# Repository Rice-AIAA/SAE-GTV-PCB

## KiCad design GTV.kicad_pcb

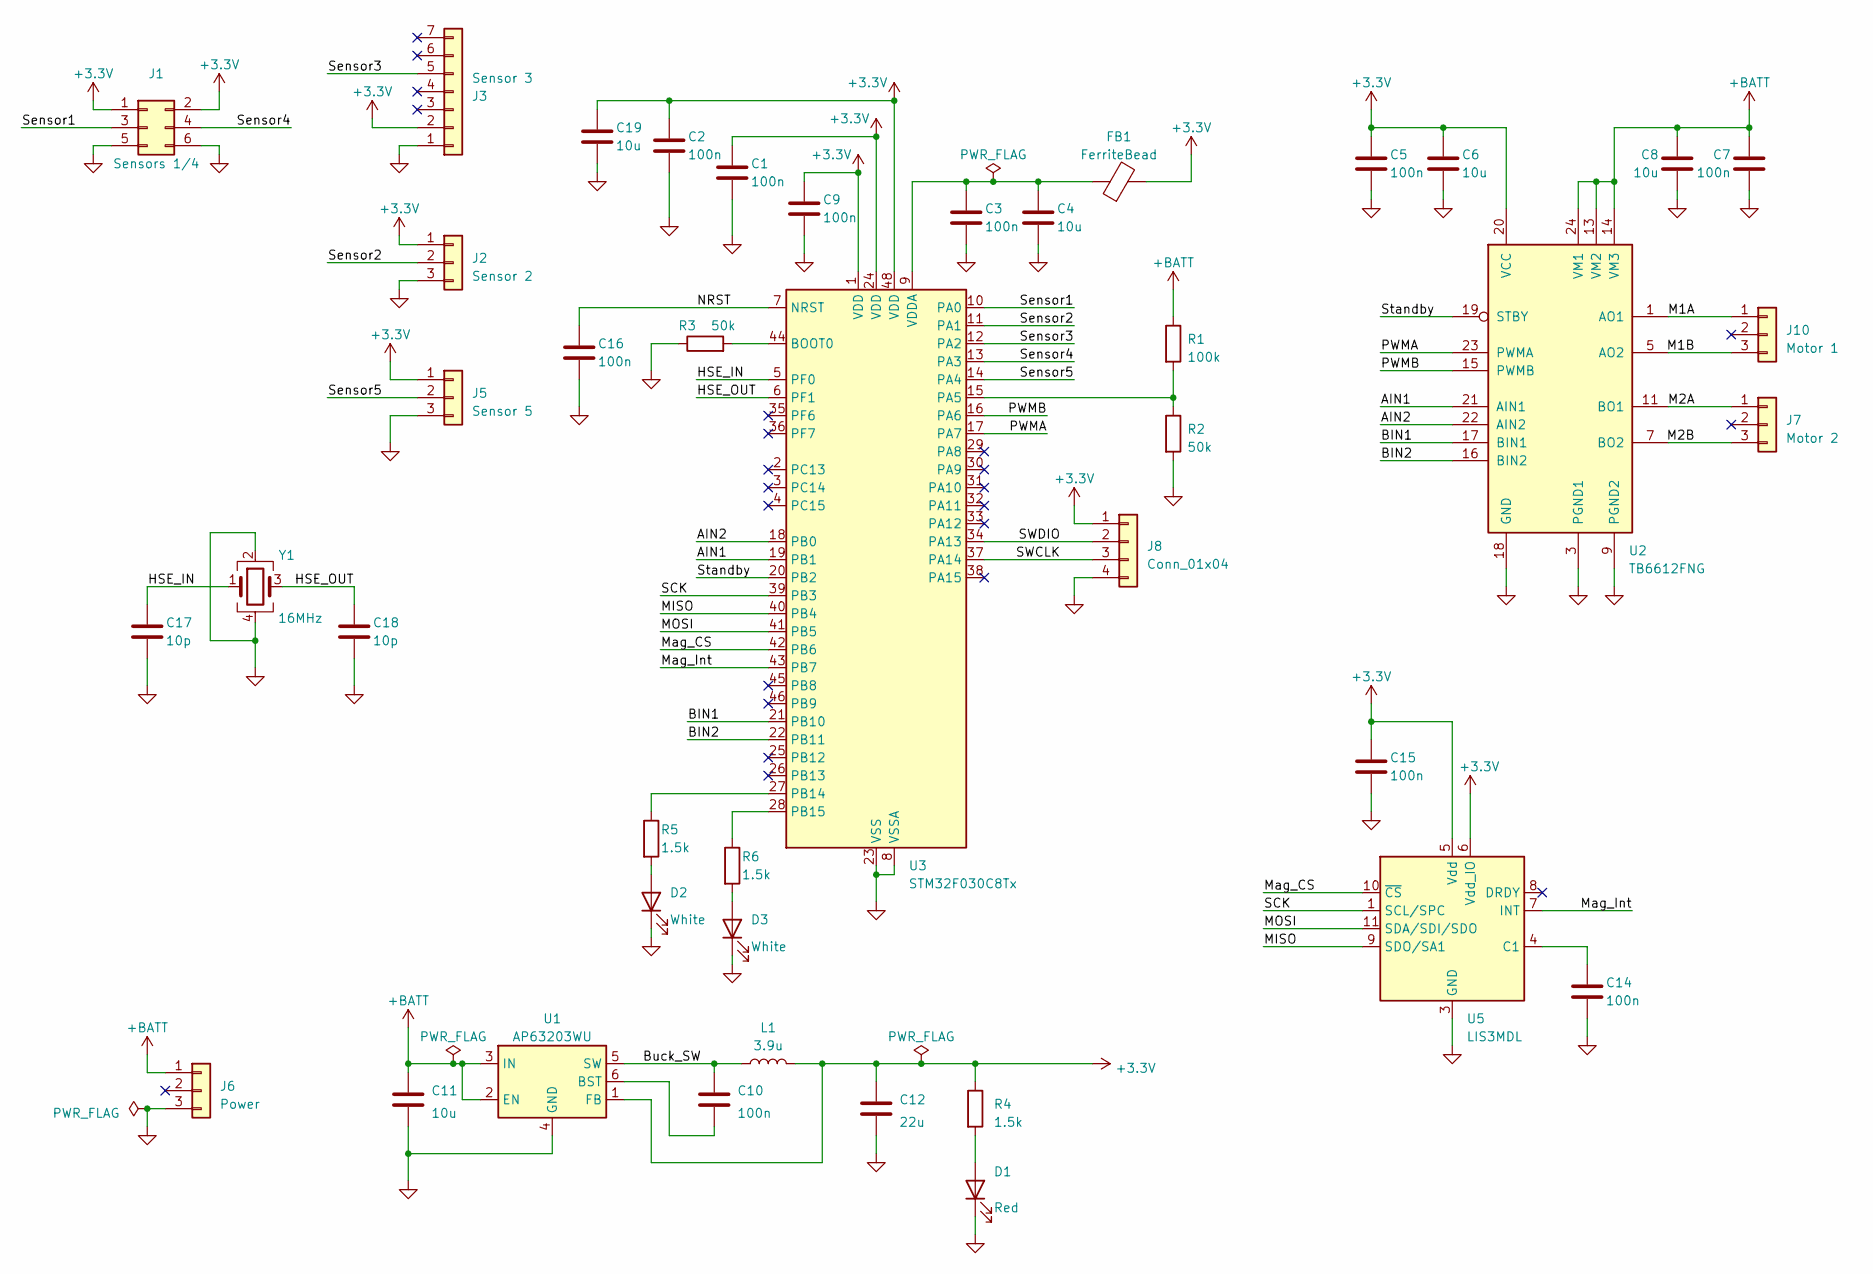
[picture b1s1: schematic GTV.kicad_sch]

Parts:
C1, C2, C3, C5, C7, C9, C10, C14, C15, C16: 100n; C_0402_1005Metric
C4, C6, C8, C19: 10u; C_0603_1608Metric
C11: 10u; C_0805_2012Metric
C12: 22u; C_0805_2012Metric
C17, C18: 10p; C_0402_1005Metric
D1: Red; LED_0603_1608Metric
D2, D3: White; LED_0603_1608Metric
FB1: FerriteBead; L_0805_2012Metric
J1: Sensors 1/4; PinHeader_2x03_P2.54mm_Vertical
J2: Sensor 2; JST_PH_B3B-PH-K_1x03_P2.00mm_Vertical
J3: Sensor 3; PinHeader_1x07_P2.54mm_Horizontal
J5: Sensor 5; JST_PH_B3B-PH-K_1x03_P2.00mm_Vertical
J6: Power; JST_PH_B3B-PH-K_1x03_P2.00mm_Vertical
J7: Motor 2; JST_PH_B3B-PH-K_1x03_P2.00mm_Vertical
J8: Conn_01x04; PinHeader_1x04_P2.54mm_Vertical
J10: Motor 1; JST_PH_B3B-PH-K_1x03_P2.00mm_Vertical
L1: 3.9u; L_Sunlord_SWPA4030S
R1: 100k; R_0402_1005Metric
R2, R3: 50k; R_0402_1005Metric
R4, R5, R6: 1.5k; R_0402_1005Metric
U1: AP63203WU; TSOT-23-6
U2: TB6612FNG; SSOP-24_5.3x8.2mm_P0.65mm
U3: STM32F030C8Tx; LQFP-48_7x7mm_P0.5mm
U5: LIS3MDL; LGA-12_2x2mm_P0.5mm
Y1: 16MHz; Crystal_SMD_3225-4Pin_3.2x2.5mm

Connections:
+3.3V: C1.1, C2.1, C5.1, C6.1, C9.1, C12.1, C15.1, C19.1, FB1.2, J1.1, J1.2, J2.1, J3.2, J5.1, J8.1, L1.2, R4.1, U1.1 (FB), U2.20 (VCC), U3.1 (VDD), U3.24 (VDD), U3.48 (VDD), U5.5 (Vdd), U5.6 (Vdd_IO)
+BATT: C7.1, C8.1, C11.1, J6.1, R1.1, U1.2 (EN), U1.3 (IN), U2.13 (VM2), U2.14 (VM3), U2.24 (VM1)
/AIN1: U2.21 (AIN1), U3.19 (PB1)
/AIN2: U2.22 (AIN2), U3.18 (PB0)
/BIN1: U2.17 (BIN1), U3.21 (PB10)
/BIN2: U2.16 (BIN2), U3.22 (PB11)
/Buck_SW: C10.1, L1.1, U1.5 (SW)
/HSE_IN: C17.1, U3.5 (PF0), Y1.1
/HSE_OUT: C18.1, U3.6 (PF1), Y1.3
/M1A: J10.1, U2.1 (AO1), U2.2 (AO1)
/M1B: J10.3, U2.5 (AO2), U2.6 (AO2)
/M2A: J7.1, U2.11 (BO1), U2.12 (BO1)
/M2B: J7.3, U2.7 (BO2), U2.8 (BO2)
/MISO: U3.40 (PB4), U5.9 (SDO/SA1)
/MOSI: U3.41 (PB5), U5.11 (SDA/SDI/SDO)
/Mag_CS: U3.42 (PB6), U5.10 (~CS)
/Mag_Int: U3.43 (PB7), U5.7 (INT)
/NRST: C16.1, U3.7 (NRST)
/PWMA: U2.23 (PWMA), U3.17 (PA7)
/PWMB: U2.15 (PWMB), U3.16 (PA6)
/SCK: U3.39 (PB3), U5.1 (SCL/SPC)
/SWCLK: J8.3, U3.37 (PA14)
/SWDIO: J8.2, U3.34 (PA13)
/Sensor1: J1.3, U3.10 (PA0)
/Sensor2: J2.2, U3.11 (PA1)
/Sensor3: J3.5, U3.12 (PA2)
/Sensor4: J1.4, U3.13 (PA3)
/Sensor5: J5.2, U3.14 (PA4)
/Standby: U2.19 (STBY), U3.20 (PB2)
GND: C1.2, C2.2, C3.2, C4.2, C5.2, C6.2, C7.2, C8.2, C9.2, C11.2, C12.2, C14.2, C15.2, C16.2, C17.2, C18.2, C19.2, D1.1 (K), D2.1 (K), D3.1 (K), J1.5, J1.6, J2.3, J3.1, J5.3, J6.3, J8.4, R2.2, R3.1, U1.4 (GND), U2.3 (PGND1), U2.4 (PGND1), U2.9 (PGND2), U2.10 (PGND2), U2.18 (GND), U3.8 (VSSA), U3.23 (VSS), U3.47 (VSS), U5.2 (GND), U5.3 (GND), U5.12 (GND), Y1.2, Y1.4
unnamed: D1.2 (A), R4.2
unnamed: D2.2 (A), R5.2
unnamed: D3.2 (A), R6.2
unnamed: C10.2, U1.6 (BST)
unnamed: R3.2, U3.44 (BOOT0)
unnamed: R1.2, R2.1, U3.15 (PA5)
unnamed: R5.1, U3.27 (PB14)
unnamed: R6.1, U3.28 (PB15)
unnamed: C3.1, C4.1, FB1.1, U3.9 (VDDA)
unnamed: C14.1, U5.4 (C1)

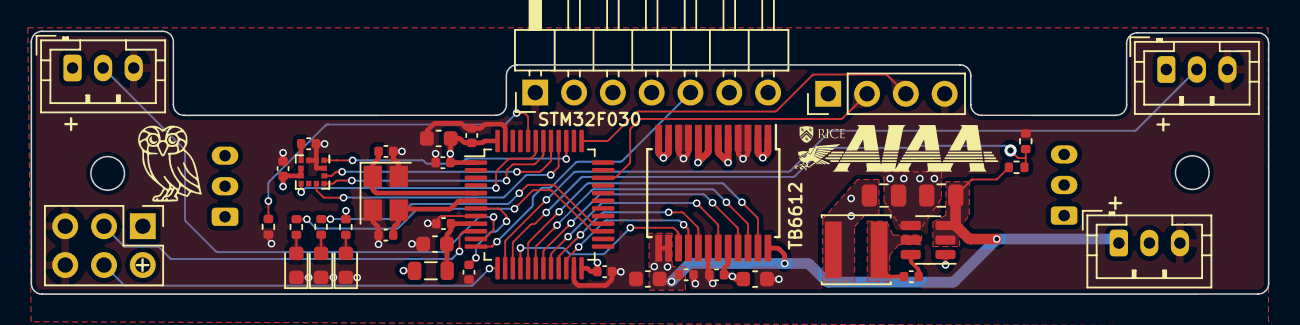
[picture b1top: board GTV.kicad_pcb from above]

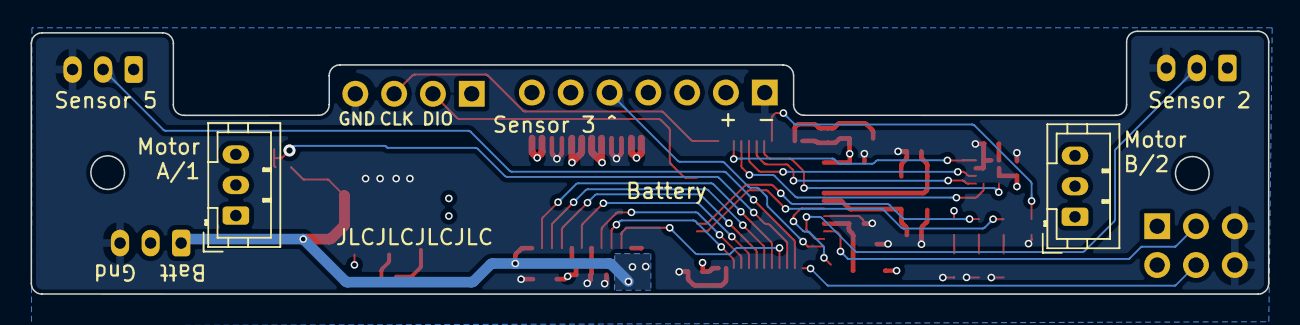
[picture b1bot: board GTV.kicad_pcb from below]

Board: 4 copper layers, 81.0 x 17.2 mm, 42 parts (2 on the bottom side), 40 nets.
